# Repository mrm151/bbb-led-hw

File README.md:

# BBBLedHW
Hardware for the beaglebone black --> stm32 --> LED light strip project

## Subsystems
* [STM32 Serial Wire Debug](#swd)
* [LED Light Strip](#leds)
* [Main Power](#5v-reg)
* [STM32 power](#3v3-reg)
* [RF network](#rf-network)
* [USB Power](#usb)

### SWD

### LEDs

### 5V Reg

### 3V3 Reg

### RF Network

### USB

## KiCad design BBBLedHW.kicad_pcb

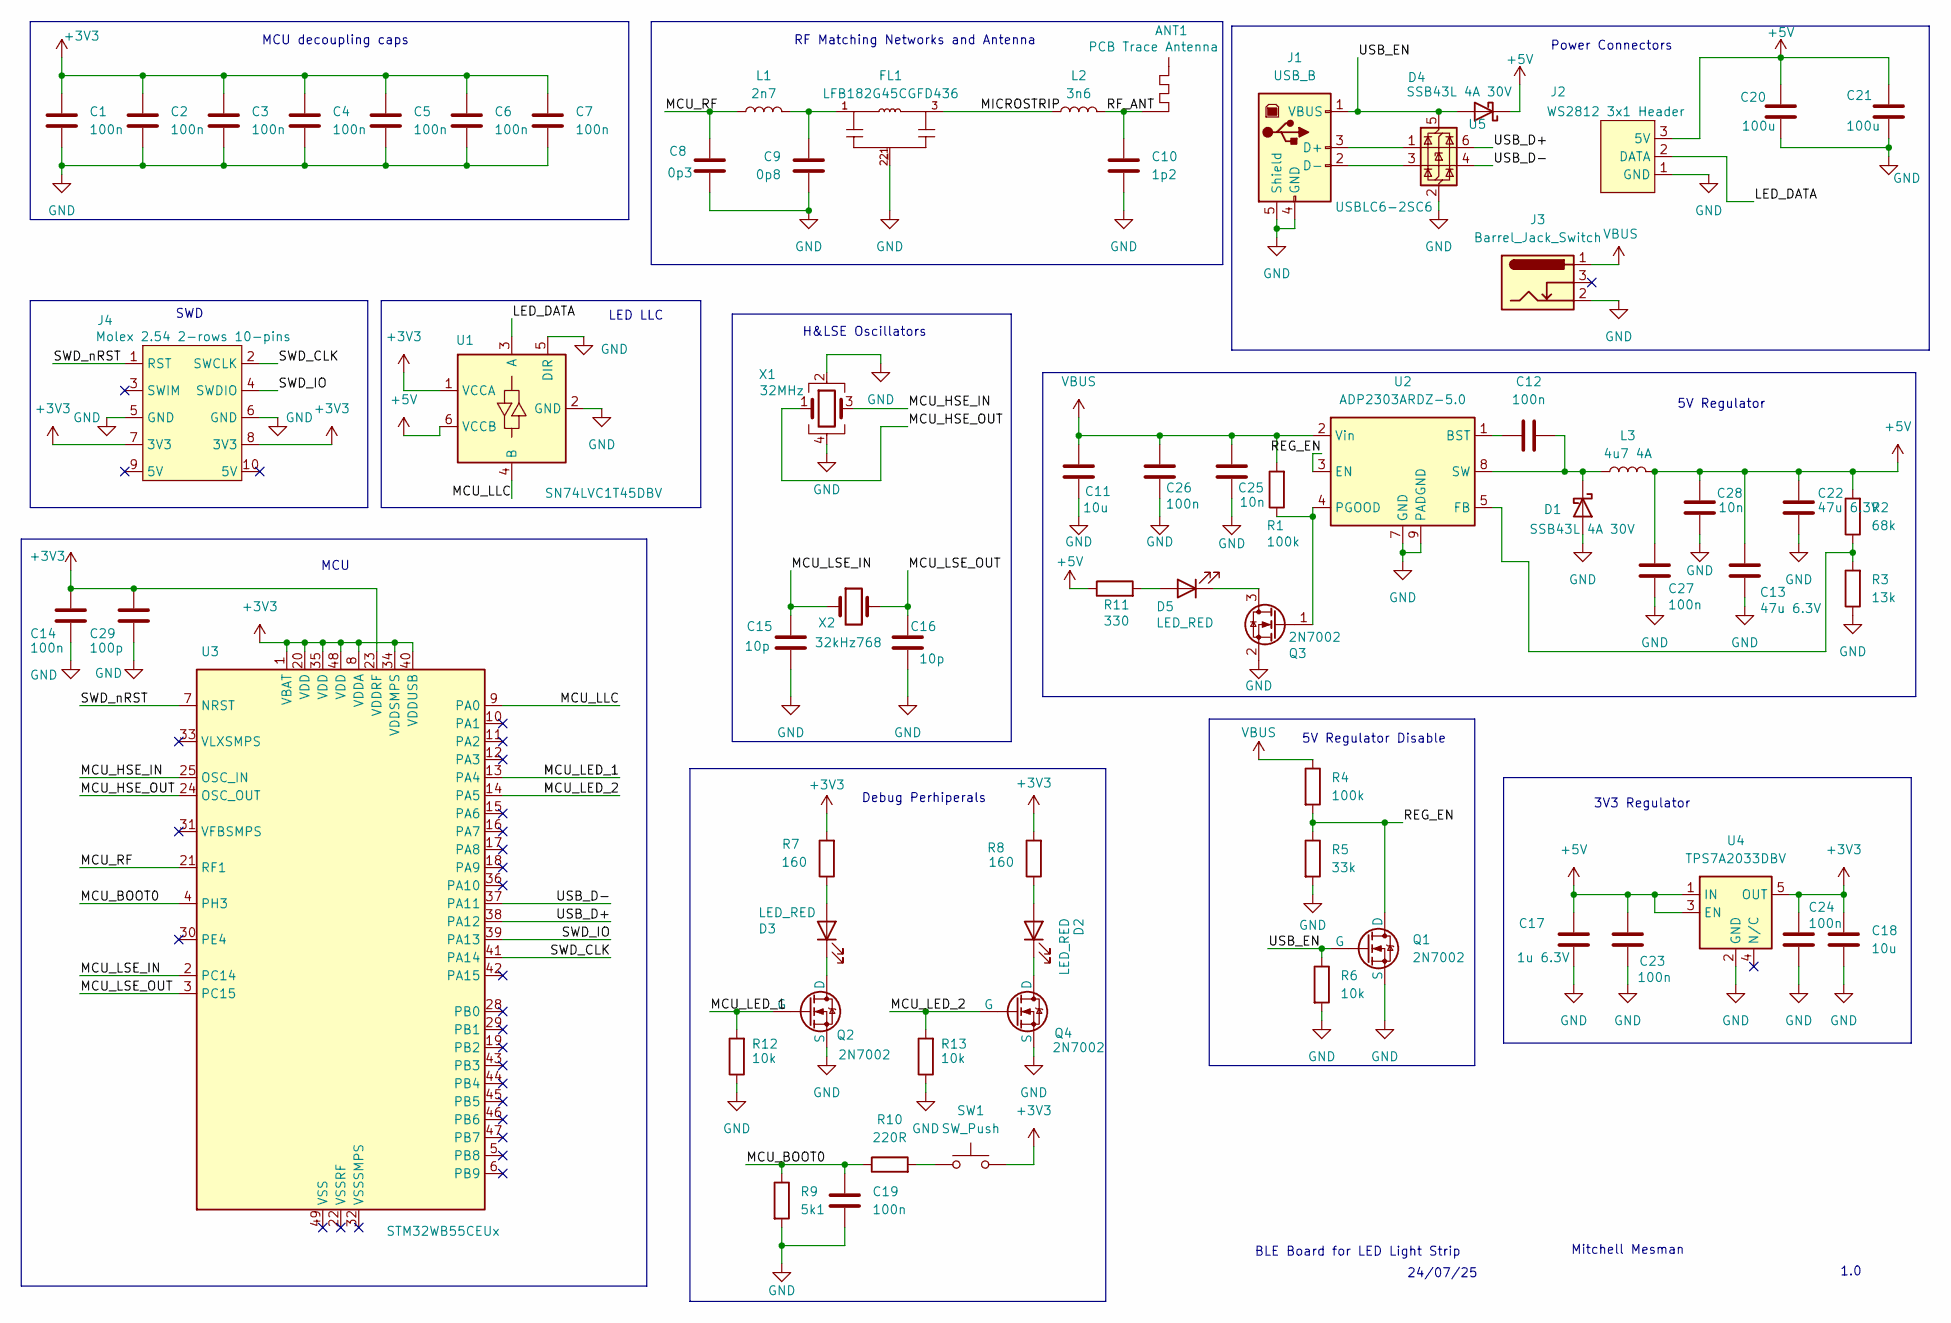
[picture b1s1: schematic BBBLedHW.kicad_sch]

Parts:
ANT1: PCB Trace Antenna; TraceAntenna
C1, C2, C3, C4, C5, C6, C7, C12, C14, C19, C23, C24, C26, C27: 100n; C_0402_1005Metric; Manufacturer Part Number KGM05AR71E104KH
C8: 0p3; C_0402_1005Metric; Manufacturer Part Number GRM1555C1HR30WA01D
C9: 0p8; C_0402_1005Metric; Manufacturer Part Number GRM1555C1HR80BA01D
C10: 1p2; C_0402_1005Metric; Manufacturer Part Number GRM1555C1H1R2WA01D
C11, C18: 10u; C_0805_2012Metric; Manufacturer Part Number GRM21BR61E106KA73K
C13, C22: 47u 6.3V; C_0805_2012Metric; Manufacturer Part Number C2012X5R0J476M125AC
C15, C16: 10p; C_0402_1005Metric; Manufacturer Part Number KGM05ACG1H100JN
C17: 1u 6.3V; C_0402_1005Metric; Manufacturer Part Number GRT155R70J105KE01D
C20, C21: 100u; WCAP-ASLI_5X5.5_DXL_; Manufacturer Part Number 865080142007
C25, C28: 10n; C_0402_1005Metric; Manufacturer Part Number CC0402KRX7R8BB103
C29: 100p; C_0402_1005Metric; Manufacturer Part Number KGM05AR71E101KH
D1, D4: SSB43L 4A 30V; DIODE_DO214AA_MBRS-L; Manufacturer Part Number SSB43L-E3/52T
D2, D3, D5: LED_RED; LED_0603_1608Metric; Manufacturer Part Number LTST-C190KRKT
FL1: LFB182G45CGFD436; FIL_LFB182G45CGFD436; PARTREV N/A
J1: USB_B; CONN_10118194-0001LF_AMP; Manufacturer Part Number 10118194-0001LF
J2: WS2812 3x1 Header
J3: Barrel_Jack_Switch; TENSILITY_54-00131; Manufacturer Part Number 54-00131
J4: Molex 2.54 2-rows 10-pins; CONN10_302-S101_OST; Manufacturer Part Number 302-S101
L1: 2n7; L_0402_1005Metric; Manufacturer Part Number LQG15HS2N7S02D
L2: 3n6; L_0402_1005Metric; Manufacturer Part Number LQG15HS3N6S02D
L3: 4u7 4A; IND_CLF10060NIT-4R7N-D; Manufacturer Part Number CLF10060NIT-4R7N-D
Q1, Q2, Q3, Q4: 2N7002; SOT-23; Manufacturer Part Number 2N7002
R1, R4: 100k; R_0402_1005Metric; Manufacturer Part Number ERA-2AEB104X
R2: 68k; R_0402_1005Metric; Manufacturer Part Number RC0402FR-0768KL
R3: 13k; R_0402_1005Metric; Manufacturer Part Number RC0402FR-0713KL
R5: 33k; R_0402_1005Metric; Manufacturer Part Number RC0402FR-1333KL
R6, R12, R13: 10k; R_0402_1005Metric; Manufacturer Part Number RC0402JR-0710KL
R7, R8: 160; R_0402_1005Metric; Manufacturer Part Number ERJ-2RKF1600X
R9: 5k1; R_0402_1005Metric; Manufacturer Part Number RC0402FR-075K1L
R10: 220R; R_0402_1005Metric; Manufacturer Part Number PFR05S-221-FNH
R11: 330; R_0402_1005Metric; Manufacturer Part Number RC0402FR-13330RL
SW1: SW_Push; SW_Push_1P1T_NO_CK_KMR2; Manufacturer Part Number KMR231G LFS
U1: SN74LVC1T45DBV; SOT-23-6; Manufacturer Part Number SN74LVC1T45DBVR
U2: ADP2303ARDZ-5.0; SOIC-8-1EP_3.9x4.9mm_P1.27mm_EP2.29x3mm; Manufacturer Part Number ADP2303ARDZ-5.0-R7
U3: STM32WB55CEUx; QFN-48-1EP_7x7mm_P0.5mm_EP5.6x5.6mm; Manufacturer Part Number STM32WB55CEU6
U4: TPS7A2033DBV; SOT-23-5; Manufacturer Part Number TPS7A2433DBVR
U5: USBLC6-2SC6; SOT-23-6; Manufacturer Part Number USBLC6-2SC6
X1: 32MHz; Crystal_SMD_2016-4Pin_2.0x1.6mm; Manufacturer Part Number ECS-320-8-37CKM
X2: 32kHz768; XTAL_NX2012SA_NDK; Manufacturer Part Number STDMUB1-32.768K

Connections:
+3V3: C1.1, C2.1, C3.1, C4.1, C5.1, C6.1, C7.1, C14.1, C18.2, C24.1, C29.1, J4.7 (3V3), J4.8 (3V3), R7.2, R8.2, SW1.2, U1.1 (VCCA), U3.1 (VBAT), U3.8 (VDDA), U3.20 (VDD), U3.23 (VDDRF), U3.34 (VDDSMPS), U3.35 (VDD), U3.40 (VDDUSB), U3.48 (VDD), U4.5 (OUT)
+5V: C13.1, C17.2, C20.1, C21.1, C22.1, C23.1, C27.1, C28.1, D4.1 (K), J2.3 (5V), L3.2, R2.2, R11.1, U1.6 (VCCB), U4.1 (IN), U4.3 (EN)
/LED_DATA: J2.2 (DATA), U1.3 (A)
/MCU_BOOT0: C19.1, R9.1, R10.1, U3.4 (PH3)
/MCU_HSE_IN: U3.25 (OSC_IN), X1.3
/MCU_HSE_OUT: U3.24 (OSC_OUT), X1.1
/MCU_LED_1: Q2.2 (G), R12.2, U3.13 (PA4)
/MCU_LED_2: Q4.2 (G), R13.2, U3.14 (PA5)
/MCU_LLC: U1.4 (B), U3.9 (PA0)
/MCU_LSE_IN: C15.1, U3.2 (PC14), X2.1
/MCU_LSE_OUT: C16.1, U3.3 (PC15), X2.2
/MCU_RF: C8.1, L1.2, U3.21 (RF1)
/MICROSTRIP: FL1.3, L2.1
/REG_EN: Q1.1 (D), R4.2, R5.1, U2.3 (EN)
/RF_ANT: ANT1., C10.1, L2.2
/SWD_CLK: J4.2 (SWCLK), U3.41 (PA14)
/SWD_IO: J4.4 (SWDIO), U3.39 (PA13)
/SWD_nRST: J4.1 (RST), U3.7 (NRST)
/USB_D+: U3.38 (PA12), U5.6 (I/O1)
/USB_D-: U3.37 (PA11), U5.4 (I/O2)
/USB_EN: D4.2 (A), J1.1 (VBUS), Q1.2 (G), R6.1, U5.5 (VBUS)
GND: C1.2, C2.2, C3.2, C4.2, C5.2, C6.2, C7.2, C8.2, C9.2, C10.2, C11.1, C13.2, C14.2, C15.2, C16.2, C17.1, C18.1, C19.2, C20.2, C21.2, C22.2, C23.2, C24.2, C25.2, C26.2, C27.2, C28.2, C29.2, D1.2 (A), FL1.2, FL1.2_1, J1.4 (GND), J1.5 (Shield), J2.1 (GND), J3.2, J4.5 (GND), J4.6 (GND), Q1.3 (S), Q2.3 (S), Q3.2 (S), Q4.3 (S), R3.1, R5.2, R6.2, R9.2, R12.1, R13.1, U1.2 (GND), U1.5 (DIR), U2.7 (GND), U2.9 (PADGND), U4.2 (GND), U5.2 (GND), X1.2, X1.4
unnamed: C9.1, FL1.1, L1.1
unnamed: C12.1, D1.1 (K), L3.1, U2.8 (SW)
unnamed: D2.2 (A), R8.1
unnamed: D2.1 (K), Q4.1 (D)
unnamed: D3.2 (A), R7.1
unnamed: D3.1 (K), Q2.1 (D)
unnamed: D5.2 (A), R11.2
unnamed: D5.1 (K), Q3.3 (D)
unnamed: J1.3 (D+), U5.1 (I/O1)
unnamed: J1.2 (D-), U5.3 (I/O2)
unnamed: Q3.1 (G), R1.1, U2.4 (PGOOD)
unnamed: R10.2, SW1.1
unnamed: C12.2, U2.1 (BST)
unnamed: R2.1, R3.2, U2.5 (FB)
VBUS: C11.2, C25.1, C26.1, J3.1, R1.2, R4.1, U2.2 (Vin)

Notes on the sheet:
Power Connectors
5V Regulator Disable
24/07/25
LED LLC
BLE Board for LED Light Strip
RF Matching Networks and Antenna
Mitchell Mesman
Debug Perhiperals
H&LSE Oscillators
3V3 Regulator
SWD
MCU
5V Regulator
1.0
MCU decoupling caps

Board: 4 copper layers, 67 parts (0 on the bottom side), 36 nets, no tracks yet.

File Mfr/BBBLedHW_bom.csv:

"Reference","Qty","Value","Footprint","MANUFACTURER","Distributor Link","Manufacturer Part Number"
"ANT1","1","PCB Trace Antenna","bbbled:TraceAntenna","","",""
"C1,C2,C3,C4,C5,C6,C7,C12,C14,C19,C23,C24,C26,C27","14","100n","Capacitor_SMD:C_0402_1005Metric","KYOCERA AVX","https://www.digikey.co.nz/en/products/detail/kyocera-avx/KGM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","KGM05AR71E104KH"
"C8","1","0p3","Capacitor_SMD:C_0402_1005Metric","Murata Electronics","https://www.digikey.co.nz/en/products/detail/murata-electron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","GRM1555C1HR30WA01D"
"C9","1","0p8","Capacitor_SMD:C_0402_1005Metric","Murata Electronics","https://www.digikey.co.nz/en/products/detail/murata-electron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","GRM1555C1HR80BA01D"
"C10","1","1p2","Capacitor_SMD:C_0402_1005Metric","Murata Electronics","https://www.digikey.co.nz/en/products/detail/murata-electron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","GRM1555C1H1R2WA01D"
"C11,C18","2","10u","Capacitor_SMD:C_0805_2012Metric","Murata Electronics","https://www.digikey.co.nz/en/products/detail/murata-electron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","GRM21BR61E106KA73K"
"C13,C22","2","47u 6.3V","Capacitor_SMD:C_0805_2012Metric","TDK Corporation","https://www.digikey.co.nz/en/products/detail/tdk-corporation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","C2012X5R0J476M125AC"
"C15,C16","2","10p","Capacitor_SMD:C_0402_1005Metric","KYOCERA AVX","https://www.digikey.co.nz/en/products/detail/kyocera-avx/KGM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","KGM05ACG1H100JN"
"C17","1","1u 6.3V","Capacitor_SMD:C_0402_1005Metric","Murata Electronics","https://www.digikey.co.nz/en/products/detail/murata-electron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","GRT155R70J105KE01D"
"C20,C21","2","100u","bbbled:WCAP-ASLI_5X5.5_DXL_","Würth Elektronik","https://www.digikey.co.nz/en/products/detail/w%C3%BCrth-elek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","865080142007"
"C25,C28","2","10n","Capacitor_SMD:C_0402_1005Metric","YAGEO","https://www.digikey.co.nz/en/products/detail/yageo/CC0402KRX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","CC0402KRX7R8BB103"
"C29","1","100p","Capacitor_SMD:C_0402_1005Metric","KYOCERA AVX","https://www.digikey.co.nz/en/products/detail/kyocera-avx/KGM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","KGM05AR71E101KH"
"D1,D4","2","SSB43L 4A 30V","bbbled:DIODE_DO214AA_MBRS-L","Vishay General Semiconductor - Diodes Division","https://www.digikey.co.nz/en/products/detail/vishay-general-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","SSB43L-E3/52T"
"D2,D3,D5","3","LED_RED","LED_SMD:LED_0603_1608Metric","Lite-On Inc.","https://www.digikey.com/en/products/detail/liteon/LTST-C190K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","LTST-C190KRKT"
"FID1,FID2,FID3","3","Fiducial","Fiducial:Fiducial_0.5mm_Mask1mm","","",""
"FL1","1","LFB182G45CGFD436","bbbled:FIL_LFB182G45CGFD436","Murata Electronics","https://www.digikey.co.nz/en/products/detail/murata-electron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","LFB182G45CGFD436"
"J1","1","USB_B","bbbled:CONN_10118194-0001LF_AMP","Amphenol ICC (FCI)","https://www.digikey.co.nz/en/products/detail/amphenol-cs-fci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","10118194-0001LF"
"J2","1","WS2812 3x1 Header","bbbled:CONN_A-6373-03A_MOL","","",""
"J3","1","Barrel_Jack_Switch","bbbled:TENSILITY_54-00131","Tensility International Corp","https://www.digikey.com/en/products/detail/tensility-interna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","54-00131"
"J4","1","Molex 2.54 2-rows 10-pins","bbbled:CONN10_302-S101_OST","On Shore Technology Inc.","https://www.digikey.co.nz/en/products/detail/on-shore-techno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","302-S101"
"L1","1","2n7","Inductor_SMD:L_0402_1005Metric","Murata Electronics","https://www.digikey.co.nz/en/products/detail/murata-electron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","LQG15HS2N7S02D"
"L2","1","3n6","Inductor_SMD:L_0402_1005Metric","Murata Electronics","https://www.digikey.co.nz/en/products/detail/murata-electron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","LQG15HS3N6S02D"
"L3","1","4u7 4A","bbbled:IND_CLF10060NIT-4R7N-D","TDK Corporation","https://www.digikey.co.nz/en/products/detail/tdk-corporation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","CLF10060NIT-4R7N-D"
"Q1,Q2,Q3,Q4","4","2N7002","Package_TO_SOT_SMD:SOT-23","onsemi","https://www.digikey.co.nz/en/products/detail/onsemi/2n7002/244345","2N7002"
"R1,R4","2","100k","Resistor_SMD:R_0402_1005Metric","Panasonic Electronic Components","https://www.digikey.co.nz/en/products/detail/panasonic-elect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","ERA-2AEB104X"
"R2","1","68k","Resistor_SMD:R_0402_1005Metric","YAGEO","https://www.digikey.co.nz/en/products/detail/yageo/RC0402FR-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","RC0402FR-0768KL"
"R3","1","13k","Resistor_SMD:R_0402_1005Metric","YAGEO","https://www.digikey.co.nz/en/products/detail/yageo/RC0402FR-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","RC0402FR-0713KL"
"R5","1","33k","Resistor_SMD:R_0402_1005Metric","YAGEO","https://www.digikey.co.nz/en/products/detail/yageo/RC0402FR-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","RC0402FR-1333KL"
"R6,R12,R13","3","10k","Resistor_SMD:R_0402_1005Metric","YAGEO","https://www.digikey.co.nz/en/products/detail/yageo/RC0402JR-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","RC0402JR-0710KL"
"R7,R8","2","160","Resistor_SMD:R_0402_1005Metric","Panasonic Electronic Components","https://www.digikey.co.nz/en/products/detail/panasonic-elect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","ERJ-2RKF1600X"
"R9","1","5k1","Resistor_SMD:R_0402_1005Metric","YAGEO","https://www.digikey.co.nz/en/products/detail/yageo/RC0402FR-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","RC0402FR-075K1L"
"R10","1","220R","Resistor_SMD:R_0402_1005Metric","Delta Electronics/Cyntec","https://www.digikey.co.nz/en/products/detail/delta-electroni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","PFR05S-221-FNH"
"R11","1","330","Resistor_SMD:R_0402_1005Metric","YAGEO","https://www.digikey.co.nz/en/products/detail/yageo/RC0402FR-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","RC0402FR-13330RL"
"SW1","1","SW_Push","Button_Switch_SMD:SW_Push_1P1T_NO_CK_KMR2","C&K","https://www.digikey.co.nz/en/products/detail/c-k/KMR231G-LFS/550477","KMR231G LFS"
"U1","1","SN74LVC1T45DBV","Package_TO_SOT_SMD:SOT-23-6","Texas Instruments","https://www.digikey.co.nz/en/products/detail/texas-instrumen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","SN74LVC1T45DBVR"
"U2","1","ADP2303ARDZ-5.0","Package_SO:SOIC-8-1EP_3.9x4.9mm_P1.27mm_EP2.29x3mm"," Analog Devices","https://www.mouser.com/ProductDetail/Analog-Devices/ADP2303A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"," ADP2303ARDZ-5.0-R7 "
"U3","1","STM32WB55CEUx","Package_DFN_QFN:QFN-48-1EP_7x7mm_P0.5mm_EP5.6x5.6mm","STMicroelectronics","https://www.digikey.co.nz/en/products/detail/stmicroelectron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","STM32WB55CEU6"
"U4","1","TPS7A2033DBV","Package_TO_SOT_SMD:SOT-23-5","Texas Instruments","https://www.digikey.co.nz/en/products/detail/texas-instrumen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","TPS7A2433DBVR"
"U5","1","USBLC6-2SC6","Package_TO_SOT_SMD:SOT-23-6","UMW","https://www.digikey.co.nz/en/products/detail/umw/usblc6-2sc6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","USBLC6-2SC6"
"X1","1","32MHz","Crystal:Crystal_SMD_2016-4Pin_2.0x1.6mm","ECS Inc.","https://www.digikey.com/en/products/detail/ecs-inc/ECS-320-8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","ECS-320-8-37CKM"
"X2","1","32kHz768","bbbled:XTAL_NX2012SA_NDK","NDK (NIHON DEMPA KOGYO CO., LTD)","https://www.digikey.com/en/products/detail/ndk-nihon-dempa-k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","STDMUB1-32.768K"

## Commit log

2025-07-24 Added 5V regulator disable circuit and DC+USB power connectors
2025-07-25 Final touches before review
2025-08-19 Add reviewed schematic
2025-08-19 Final touches before assigning footprints
2025-08-19 need to find a way to remove these other files from the repo...
2025-09-03 Chosen components, footprints, 3d models and PCB constraints. Next step - placing and routing!
2025-09-03 Remove files
2025-09-03 Skeleton for design
2025-09-24 Add Rev1 Gerbers
2025-09-24 Rev1 visuals
2025-09-24 Remove zip file
2025-09-24 Add some resources used in RF network design
